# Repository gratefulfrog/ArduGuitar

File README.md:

The ArduGuitar 
==========

Following Microsoft's purchase of Github, this project has migrated to gitlab.

*Electric guitars with Pyboards or Arduinos inside* 

by gratefulfrog on www.arduguitar.org

V2 is now nearly ready with a new, super evolved circuit allowing nearly limitless possiblities (2015 06).  

Although, that seemed true at the time (June 2015), it took another year to get to the first workable version of both the hardware and the software!  As of 4 September 2016, we have bench tested v0.99 of the PyGuitar software and will soon put that sw on the hardware and give it a go! 

The new circuit is  driven by a [Micropython Pyboard](http://micropython.org/).

The whole story is documented [here](https://docs.google.com/document/d/1oo2Q_3ezPv_WPeJZZisc5ifhc270i9kwir6oPctKts0/edit?usp=sharing)!

-------------

V1.1 : ArduStomp and ArduGuitar updated functionality

The ArduStomp pedal interface works well and the updated Android GUI does too!

Now ready to move on to Ardu2 !
-------------

V1.0 : a fully functional Android App with Automation capability!

The sound is near perfect, there are no known bugs! 

Now using a heavily shielded Sparkfun BlueSMIRF bluetooth board and micro_protocol_03 at 115200 baud.

-------------

V0.0 : A working Android App controlling an electric guitar!

The Processing code in the android directory works with the Arduino Micro code in the micro_protocol_02 directory to collectively form the first major milestone of the project: A fully functional android app communicating with the Ibanez RG140 circuit. 

The circuit is controled by an arduino "Micro" and communicates via a JY-MCU bluetooth module.  
        
The Processing code is based on the linux python version in the linux directory. The Ketai Processing library is used for android and bluetooth support.
        
There are too many people to thank individually for all the help and support that they gave me during this work, but the core team of Blake, Enrico, Jean and Luis really made this project possible. The Brussels Hackerspace community also provided great ideas to advance the work.

My profound thanks to them and to all the others!

Now using SSH 2016 12 24

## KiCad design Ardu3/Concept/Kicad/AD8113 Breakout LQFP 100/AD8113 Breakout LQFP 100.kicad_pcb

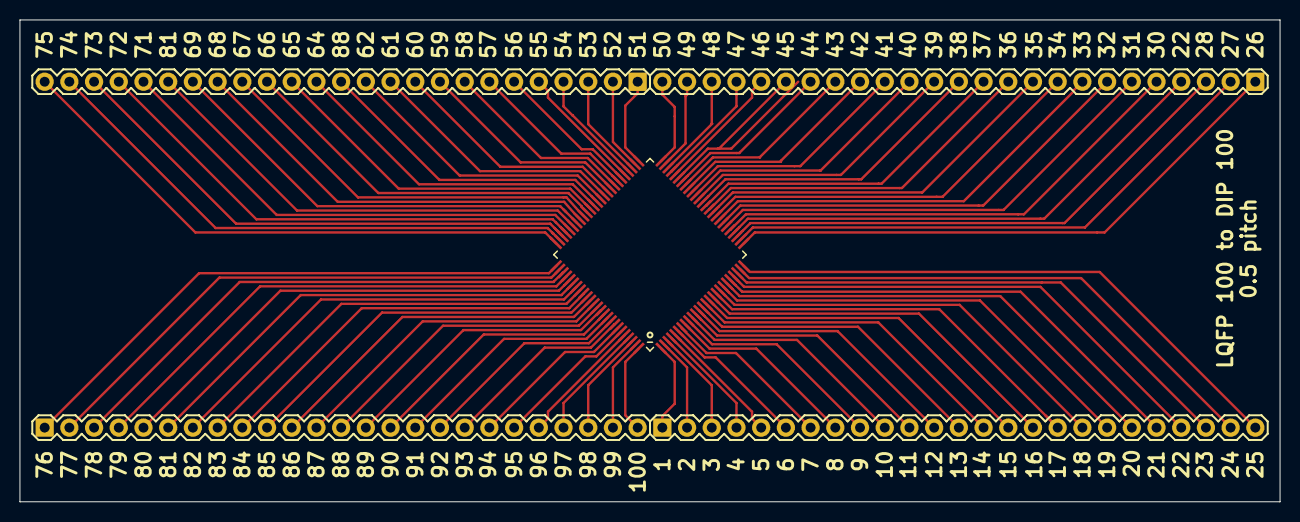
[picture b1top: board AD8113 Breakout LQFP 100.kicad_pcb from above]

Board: 2 copper layers, 129.5 x 49.5 mm, 5 parts (0 on the bottom side), 100 nets.

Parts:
J1, J2, J3, J4: Conn_01x25_Male; 1X25
U1: AD8113JST; AD8113JSTZ

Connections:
/P001: J1.1, U1.1
/P002: J1.2, U1.2
/P003: J1.3, U1.3
/P004: J1.4, U1.4
/P005: J1.5, U1.5
/P006: J1.6, U1.6
/P007: J1.7, U1.7
/P008: J1.8, U1.8
/P009: J1.9, U1.9
/P010: J1.10, U1.10
/P011: J1.11, U1.11
/P012: J1.12, U1.12
/P013: J1.13, U1.13
/P014: J1.14, U1.14
/P015: J1.15, U1.15
/P016: J1.16, U1.16
/P017: J1.17, U1.17
/P018: J1.18, U1.18
/P019: J1.19, U1.19
/P020: J1.20, U1.20
/P021: J1.21, U1.21
/P022: J1.22, U1.22
/P023: J1.23, U1.23
/P024: J1.24, U1.24
/P025: J1.25, U1.25
/P026: J2.1, U1.26
/P027: J2.2, U1.27
/P028: J2.3, U1.28
/P029: J2.4, U1.29
/P030: J2.5, U1.30
/P031: J2.6, U1.31
/P032: J2.7, U1.32
/P033: J2.8, U1.33
/P034: J2.9, U1.34
/P035: J2.10, U1.35
/P036: J2.11, U1.36
/P037: J2.12, U1.37
/P038: J2.13, U1.38
/P039: J2.14, U1.39
/P040: J2.15, U1.40
/P041: J2.16, U1.41
/P042: J2.17, U1.42
/P043: J2.18, U1.43
/P044: J2.19, U1.44
/P045: J2.20, U1.45
/P046: J2.21, U1.46
/P047: J2.22, U1.47
/P048: J2.23, U1.48
/P049: J2.24, U1.49
/P050: J2.25, U1.50
/P051: J3.1, U1.51
/P052: J3.2, U1.52
/P053: J3.3, U1.53
/P054: J3.4, U1.54
/P055: J3.5, U1.55
/P056: J3.6, U1.56
/P057: J3.7, U1.57
/P058: J3.8, U1.58
/P059: J3.9, U1.59
/P060: J3.10, U1.60
/P061: J3.11, U1.61
/P062: J3.12, U1.62
/P063: J3.13, U1.63
/P064: J3.14, U1.64
/P065: J3.15, U1.65
/P066: J3.16, U1.66
/P067: J3.17, U1.67
/P068: J3.18, U1.68
/P069: J3.19, U1.69
/P070: J3.20, U1.70
/P071: J3.21, U1.71
/P072: J3.22, U1.72
/P073: J3.23, U1.73
/P074: J3.24, U1.74
/P075: J3.25, U1.75
/P076: J4.1, U1.76
/P077: J4.2, U1.77
/P078: J4.3, U1.78
/P079: J4.4, U1.79
/P080: J4.5, U1.80
/P081: J4.6, U1.81
/P082: J4.7, U1.82
/P083: J4.8, U1.83
/P084: J4.9, U1.84
/P085: J4.10, U1.85
/P086: J4.11, U1.86
/P087: J4.12, U1.87
/P088: J4.13, U1.88
/P089: J4.14, U1.89
/P090: J4.15, U1.90
/P091: J4.16, U1.91
/P092: J4.17, U1.92
/P093: J4.18, U1.93
/P094: J4.19, U1.94
/P095: J4.20, U1.95
/P096: J4.21, U1.96
/P097: J4.22, U1.97
/P098: J4.23, U1.98
/P099: J4.24, U1.99
/P100: J4.25, U1.100

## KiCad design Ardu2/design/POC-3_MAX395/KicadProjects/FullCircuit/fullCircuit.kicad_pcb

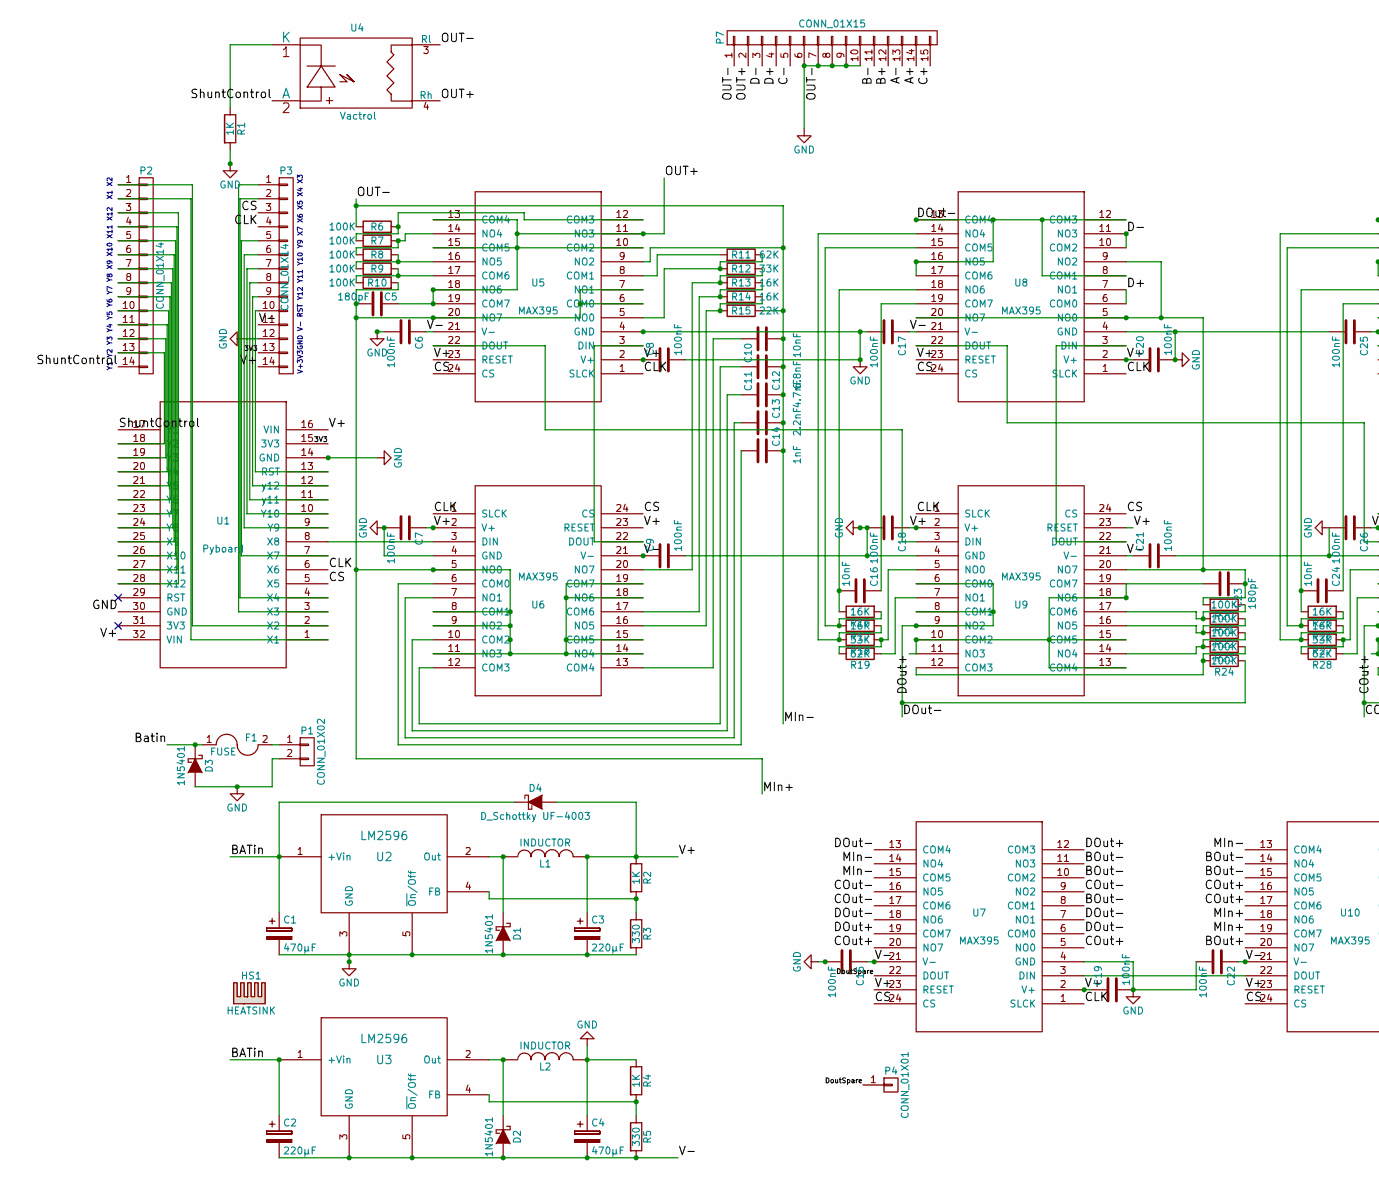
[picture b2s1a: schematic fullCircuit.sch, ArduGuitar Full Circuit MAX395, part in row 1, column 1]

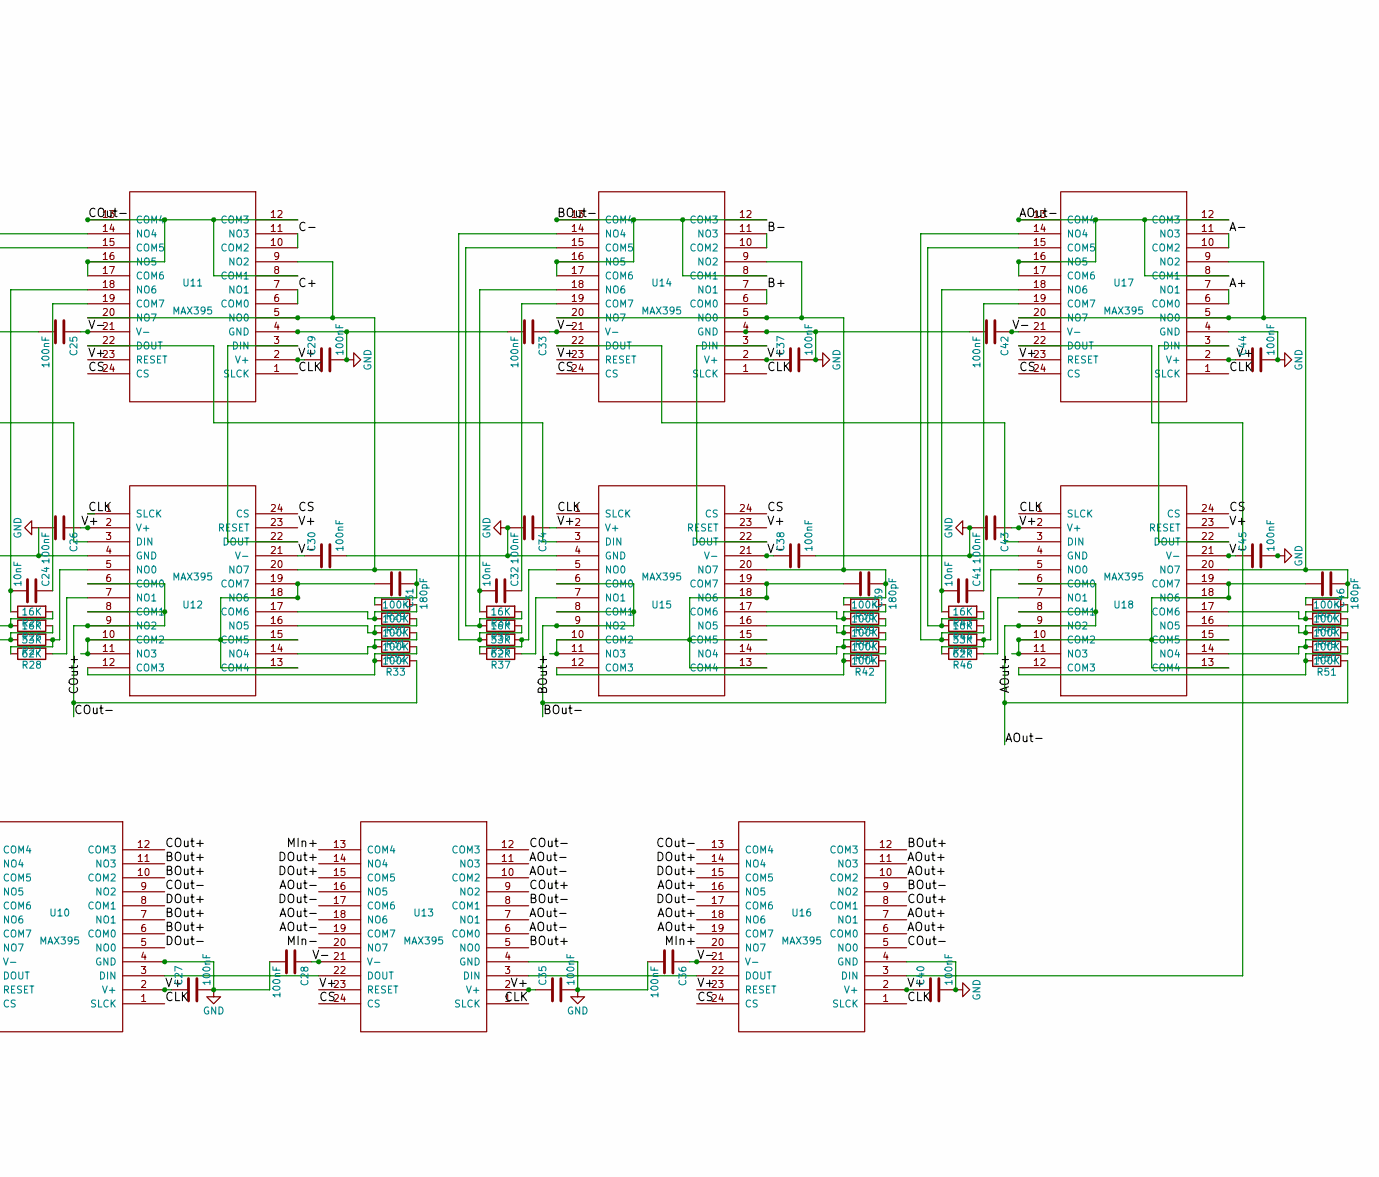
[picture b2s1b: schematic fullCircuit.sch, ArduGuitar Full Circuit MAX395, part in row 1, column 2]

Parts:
C1, C4: 470µF; C_Radial_D10_L16_P5
C2, C3: 220µF; C_Radial_D8_L11.5_P3.5
C5, C23, C31, C39, C46: 180pF; C_Disc_D3_P2.5
C6, C7, C8, C9, C15, C17, C18, C19, C20, C21, C22, C25, C26, C27, C28, C29, C30, C33, C34, C35, C36, C37, C38, C40, C42, C43, C44, C45: 100nF; C_Disc_D3_P2.5
C10, C16, C24, C32, C41: 10nF; C_Disc_D6_P5
C11: 6.8nF; C_Disc_D6_P5
C12: 4.7nF; C_Disc_D6_P5
C13: 2.2nF; C_Disc_D6_P5
C14: 1nF; C_Disc_D6_P5
D1, D2, D3: 1N5401; Diode_DO-201AD_Horizontal_RM15
D4: D_Schottky UF-4003; Diode_DO-41_SOD81_Horizontal_RM10
F1: FUSE; Fuse_TE5_Littlefuse-395Series
HS1: HEATSINK; Heatsink_TO_220_38_20
L1, L2: INDUCTOR; 330L-Q9N_Inductor
P1: CONN_01X02; PINHEAD1-2
P2, P3: CONN_01X14; Pin_Header_Straight_1x14
P4: CONN_01X01; Pin_Header_Straight_1x01
P7: CONN_01X15; DB_15F-VGA_00_BOB
R1, R2, R4: 1K; Resistor_Horizontal_RM10mm
R3, R5: 330; Resistor_Horizontal_RM10mm
R6, R7, R8, R9, R10, R20, R21, R22, R23, R24, R29, R30, R31, R32, R33, R38, R39, R40, R41, R42, R47, R48, R49, R50, R51: 100K; Resistor_Horizontal_RM10mm
R11, R19, R28, R37, R46: 62K; Resistor_Horizontal_RM10mm
R12, R18, R27, R36, R45: 33K; Resistor_Horizontal_RM10mm
R13, R14, R16, R17, R25, R26, R34, R35, R43, R44: 16K; Resistor_Horizontal_RM10mm
R15: 22K; Resistor_Horizontal_RM10mm
U1: Pyboard; Pyboard16x2
U2, U3: LM2596; T05D
U4: Vactrol
U5, U6, U7, U8, U9, U10, U11, U12, U13, U14, U15, U16, U17, U18: MAX395; DIP-24__300_pads_70_10

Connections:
/3V3: P3.13, U1.15 (3V3)
/A+: P7.14, U17.6 (COM0), U17.7 (NO1)
/A-: P7.13, U17.10 (COM2), U17.11 (NO3)
/AOut+: C46.2, U16.6 (COM0), U16.7 (NO1), U16.10 (COM2), U16.11 (NO3), U16.16 (NO5), U16.18 (NO6), U16.19 (COM7), U18.10 (COM2), U18.11 (NO3), U18.13 (COM4), U18.15 (COM5), U18.18 (NO6), U18.19 (COM7)
/AOut-: R51.1, U13.6 (COM0), U13.7 (NO1), U13.10 (COM2), U13.11 (NO3), U13.16 (NO5), U13.18 (NO6), U13.19 (COM7), U17.8 (COM1), U17.12 (COM3), U17.13 (COM4), U17.16 (NO5), U17.17 (COM6), U18.6 (COM0), U18.8 (COM1), U18.9 (NO2)
/B+: P7.12, U14.6 (COM0), U14.7 (NO1)
/B-: P7.11, U14.10 (COM2), U14.11 (NO3)
/BATin: C1.1, C2.1, D3.1 (K), D4.1 (K), F1.1, U2.1 (+Vin), U3.1 (+Vin)
/BOut+: C39.2, U10.6 (COM0), U10.7 (NO1), U10.10 (COM2), U10.11 (NO3), U10.20 (NO7), U13.5 (NO0), U15.10 (COM2), U15.11 (NO3), U15.13 (COM4), U15.15 (COM5), U15.18 (NO6), U15.19 (COM7), U16.12 (COM3)
/BOut-: R42.1, U7.8 (COM1), U7.10 (COM2), U7.11 (NO3), U10.14 (NO4), U10.15 (COM5), U13.8 (COM1), U14.8 (COM1), U14.12 (COM3), U14.13 (COM4), U14.16 (NO5), U14.17 (COM6), U15.6 (COM0), U15.8 (COM1), U15.9 (NO2), U16.9 (NO2)
/C+: P7.15, U11.6 (COM0), U11.7 (NO1)
/C-: P7.5, U11.10 (COM2), U11.11 (NO3)
/CLK: P3.4, U1.6 (X6), U5.1 (SLCK), U6.1 (SLCK), U7.1 (SLCK), U8.1 (SLCK), U9.1 (SLCK), U10.1 (SLCK), U11.1 (SLCK), U12.1 (SLCK), U13.1 (SLCK), U14.1 (SLCK), U15.1 (SLCK), U16.1 (SLCK), U17.1 (SLCK), U18.1 (SLCK)
/COut+: C31.2, U7.5 (NO0), U7.20 (NO7), U10.12 (COM3), U10.16 (NO5), U10.17 (COM6), U12.10 (COM2), U12.11 (NO3), U12.13 (COM4), U12.15 (COM5), U12.18 (NO6), U12.19 (COM7), U13.9 (NO2), U16.8 (COM1)
/COut-: R33.1, U7.9 (NO2), U7.16 (NO5), U7.17 (COM6), U10.9 (NO2), U11.8 (COM1), U11.12 (COM3), U11.13 (COM4), U11.16 (NO5), U11.17 (COM6), U12.6 (COM0), U12.8 (COM1), U12.9 (NO2), U13.12 (COM3), U16.5 (NO0), U16.13 (COM4)
/CS: P3.3, U1.5 (X5), U5.24 (CS), U6.24 (CS), U7.24 (CS), U8.24 (CS), U9.24 (CS), U10.24 (CS), U11.24 (CS), U12.24 (CS), U13.24 (CS), U14.24 (CS), U15.24 (CS), U16.24 (CS), U17.24 (CS), U18.24 (CS)
/D+: P7.4, U8.6 (COM0), U8.7 (NO1)
/D-: P7.3, U8.10 (COM2), U8.11 (NO3)
/DOut+: C23.2, U7.12 (COM3), U7.19 (COM7), U9.10 (COM2), U9.11 (NO3), U9.13 (COM4), U9.15 (COM5), U9.18 (NO6), U9.19 (COM7), U10.8 (COM1), U13.14 (NO4), U13.15 (COM5), U16.14 (NO4), U16.15 (COM5)
/DOut-: R24.1, U7.6 (COM0), U7.7 (NO1), U7.13 (COM4), U7.18 (NO6), U8.8 (COM1), U8.12 (COM3), U8.13 (COM4), U8.16 (NO5), U8.17 (COM6), U9.6 (COM0), U9.8 (COM1), U9.9 (NO2), U10.5 (NO0), U13.17 (COM6), U16.17 (COM6)
/DoutSpare: P4.1, U7.22 (DOUT)
/MIn+: C5.1, R10.2, U5.6 (COM0), U5.7 (NO1), U5.20 (NO7), U6.5 (NO0), U6.8 (COM1), U6.9 (NO2), U6.11 (NO3), U6.14 (NO4), U6.15 (COM5), U6.18 (NO6), U6.19 (COM7), U10.18 (NO6), U10.19 (COM7), U13.13 (COM4), U16.20 (NO7)
/OUT+: C5.2, P7.2, U4.4 (Rh), U5.10 (COM2), U5.11 (NO3), U5.13 (COM4), U5.15 (COM5), U5.18 (NO6), U5.19 (COM7)
/ShuntControl: P2.14, U1.17 (Y1), U4.2 (A)
/V+: C3.1, C7.1, C8.1, C18.1, C19.1, C20.1, C26.1, C27.1, C29.1, C34.1, C35.1, C37.1, C40.1, C43.1, C44.1, D4.2 (A), L1.2, P3.14, R2.1, U1.16 (VIN), U1.32 (VIN), U5.2 (V+), U5.23 (RESET), U6.2 (V+), U6.23 (RESET), U7.2 (V+), U7.23 (RESET), U8.2 (V+), U8.23 (RESET), U9.2 (V+), U9.23 (RESET), U10.2 (V+), U10.23 (RESET), U11.2 (V+), U11.23 (RESET), U12.2 (V+), U12.23 (RESET), U13.2 (V+), U13.23 (RESET), U14.2 (V+), U14.23 (RESET), U15.2 (V+), U15.23 (RESET), U16.2 (V+), U16.23 (RESET), U17.2 (V+), U17.23 (RESET), U18.2 (V+), U18.23 (RESET)
/V-: C2.2, C4.2, C6.1, C9.1, C15.1, C17.1, C21.1, C22.1, C25.1, C28.1, C30.1, C33.1, C36.1, C38.1, C42.1, C45.1, D2.2 (A), P3.11, R5.2, U3.3 (GND), U3.5 (~On~/Off), U5.21 (V-), U6.21 (V-), U7.21 (V-), U8.21 (V-), U9.21 (V-), U10.21 (V-), U11.21 (V-), U12.21 (V-), U13.21 (V-), U14.21 (V-), U15.21 (V-), U16.21 (V-), U17.21 (V-), U18.21 (V-)
unnamed: C10.1, U6.13 (COM4)
unnamed: C11.1, U6.12 (COM3)
unnamed: C12.2, U6.10 (COM2)
unnamed: C13.2, U6.7 (NO1)
unnamed: C14.2, U6.6 (COM0)
unnamed: C16.1, U8.19 (COM7)
unnamed: C16.2, R16.1, U8.18 (NO6)
unnamed: C23.1, R20.2, U8.5 (NO0), U8.9 (NO2), U8.20 (NO7), U9.20 (NO7)
unnamed: C24.1, U11.19 (COM7)
unnamed: C24.2, R25.1, U11.18 (NO6)
unnamed: C31.1, R29.2, U11.5 (NO0), U11.9 (NO2), U11.20 (NO7), U12.20 (NO7)
unnamed: C32.1, U14.19 (COM7)
unnamed: C32.2, R34.1, U14.18 (NO6)
unnamed: C39.1, R38.2, U14.5 (NO0), U14.9 (NO2), U14.20 (NO7), U15.20 (NO7)
unnamed: C41.1, U17.19 (COM7)
unnamed: C41.2, R43.1, U17.18 (NO6)
unnamed: C46.1, R47.2, U17.5 (NO0), U17.9 (NO2), U17.20 (NO7), U18.20 (NO7)
unnamed: D1.1 (K), L1.1, U2.2 (Out)
unnamed: D2.1 (K), L2.1, U3.2 (Out)
unnamed: F1.2, P1.1
unnamed: P2.1, U1.2 (X2)
unnamed: P2.2, U1.1 (X1)
unnamed: P2.3, U1.28 (X12)
unnamed: P2.4, U1.27 (X11)
unnamed: P2.5, U1.26 (X10)
unnamed: P2.6, U1.25 (X9)
unnamed: P2.7, U1.24 (Y8)
unnamed: P2.8, U1.23 (Y7)
unnamed: P2.9, U1.22 (Y6)
unnamed: P2.10, U1.21 (Y5)
unnamed: P2.11, U1.20 (Y4)
unnamed: P2.12, U1.19 (Y3)
unnamed: P2.13, U1.18 (Y2)
unnamed: P3.1, U1.3 (X3)
unnamed: P3.2, U1.4 (X4)
unnamed: P3.5, U1.7 (X7)
unnamed: P3.7, U1.10 (Y10)
unnamed: P3.8, U1.11 (y11)
unnamed: P3.9, U1.12 (y12)
unnamed: P3.10, U1.13 (RST)
unnamed: R1.1, U4.1 (K)
unnamed: R2.2, R3.1, U2.4 (FB)
unnamed: R4.2, R5.1, U3.4 (FB)
unnamed: R6.2, R7.1, U5.12 (COM3)
unnamed: R7.2, R8.1, U5.14 (NO4)
unnamed: R8.2, R9.1, U5.16 (NO5)
unnamed: R9.2, R10.1, U5.17 (COM6)
unnamed: R11.1, R12.2, U5.5 (NO0)
unnamed: R11.2, U5.8 (COM1)
unnamed: R12.1, R13.2, U6.20 (NO7)
unnamed: R13.1, R14.2, U6.17 (COM6)
unnamed: R14.1, R15.2, U6.16 (NO5)
unnamed: R16.2, R17.1, U8.15 (COM5)
unnamed: R17.2, R18.1, U8.14 (NO4)
unnamed: R18.2, R19.1, U9.5 (NO0)
unnamed: R19.2, U9.7 (NO1)
unnamed: R20.1, R21.2, U9.17 (COM6)
unnamed: R21.1, R22.2, U9.16 (NO5)
unnamed: R22.1, R23.2, U9.14 (NO4)
unnamed: R23.1, R24.2, U9.12 (COM3)
unnamed: R25.2, R26.1, U11.15 (COM5)
unnamed: R26.2, R27.1, U11.14 (NO4)
unnamed: R27.2, R28.1, U12.5 (NO0)
unnamed: R28.2, U12.7 (NO1)
unnamed: R29.1, R30.2, U12.17 (COM6)
unnamed: R30.1, R31.2, U12.16 (NO5)
unnamed: R31.1, R32.2, U12.14 (NO4)
unnamed: R32.1, R33.2, U12.12 (COM3)
unnamed: R34.2, R35.1, U14.15 (COM5)
unnamed: R35.2, R36.1, U14.14 (NO4)
unnamed: R36.2, R37.1, U15.5 (NO0)
unnamed: R37.2, U15.7 (NO1)
unnamed: R38.1, R39.2, U15.17 (COM6)
unnamed: R39.1, R40.2, U15.16 (NO5)
unnamed: R40.1, R41.2, U15.14 (NO4)
unnamed: R41.1, R42.2, U15.12 (COM3)
unnamed: R43.2, R44.1, U17.15 (COM5)
unnamed: R44.2, R45.1, U17.14 (NO4)
unnamed: R45.2, R46.1, U18.5 (NO0)
unnamed: R46.2, U18.7 (NO1)
unnamed: R47.1, R48.2, U18.17 (COM6)
unnamed: R48.1, R49.2, U18.16 (NO5)
unnamed: R49.1, R50.2, U18.14 (NO4)
unnamed: R50.1, R51.2, U18.12 (COM3)
unnamed: U1.8 (X8), U6.3 (DIN)
unnamed: U5.3 (DIN), U6.22 (DOUT)
unnamed: U5.22 (DOUT), U9.3 (DIN)
unnamed: U8.3 (DIN), U9.22 (DOUT)
unnamed: U10.3 (DIN), U13.22 (DOUT)
unnamed: U7.3 (DIN), U10.22 (DOUT)
unnamed: U11.3 (DIN), U12.22 (DOUT)
unnamed: U11.22 (DOUT), U15.3 (DIN)
unnamed: U8.22 (DOUT), U12.3 (DIN)
unnamed: U13.3 (DIN), U16.22 (DOUT)
unnamed: U14.3 (DIN), U15.22 (DOUT)
unnamed: U14.22 (DOUT), U18.3 (DIN)
unnamed: U16.3 (DIN), U17.22 (DOUT)
unnamed: U17.3 (DIN), U18.22 (DOUT)

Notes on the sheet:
Y1 Y2 Y3 Y4 Y5 Y6 Y7 Y8 X9 X10 X11 X12 X1 X2
V+3V3GND V- RST Y12 Y11 Y10 Y9 X7 X6 X5 X4 X3

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
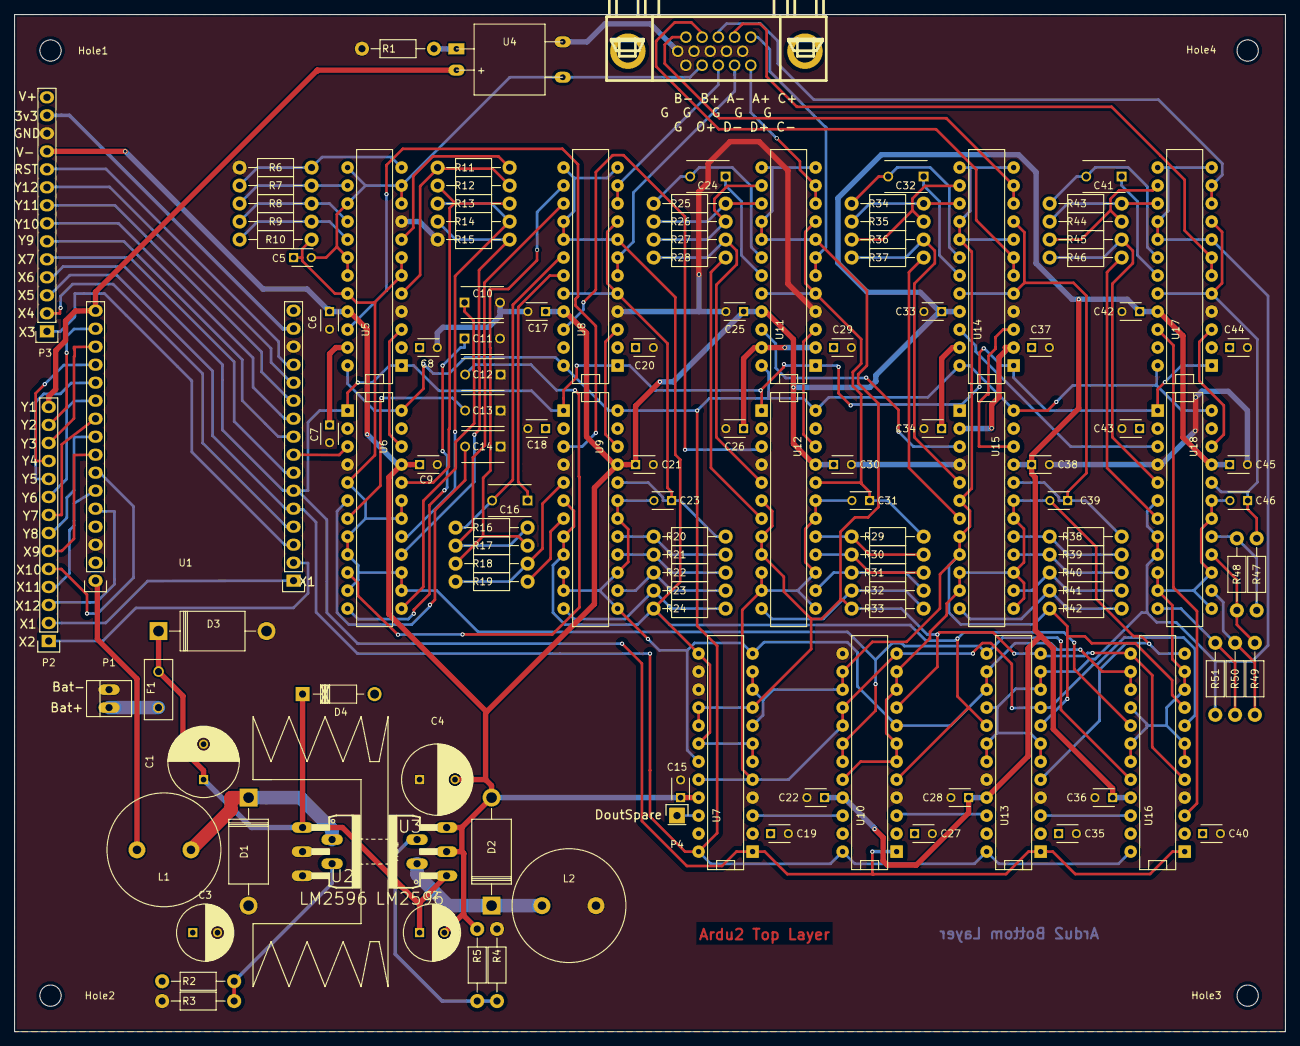
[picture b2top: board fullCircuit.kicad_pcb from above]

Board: 2 copper layers, 179.3 x 143.5 mm, 132 parts (0 on the bottom side), 126 nets.

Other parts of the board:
Hole1, Hole2, Hole3, Hole4: MountingHole_3mm

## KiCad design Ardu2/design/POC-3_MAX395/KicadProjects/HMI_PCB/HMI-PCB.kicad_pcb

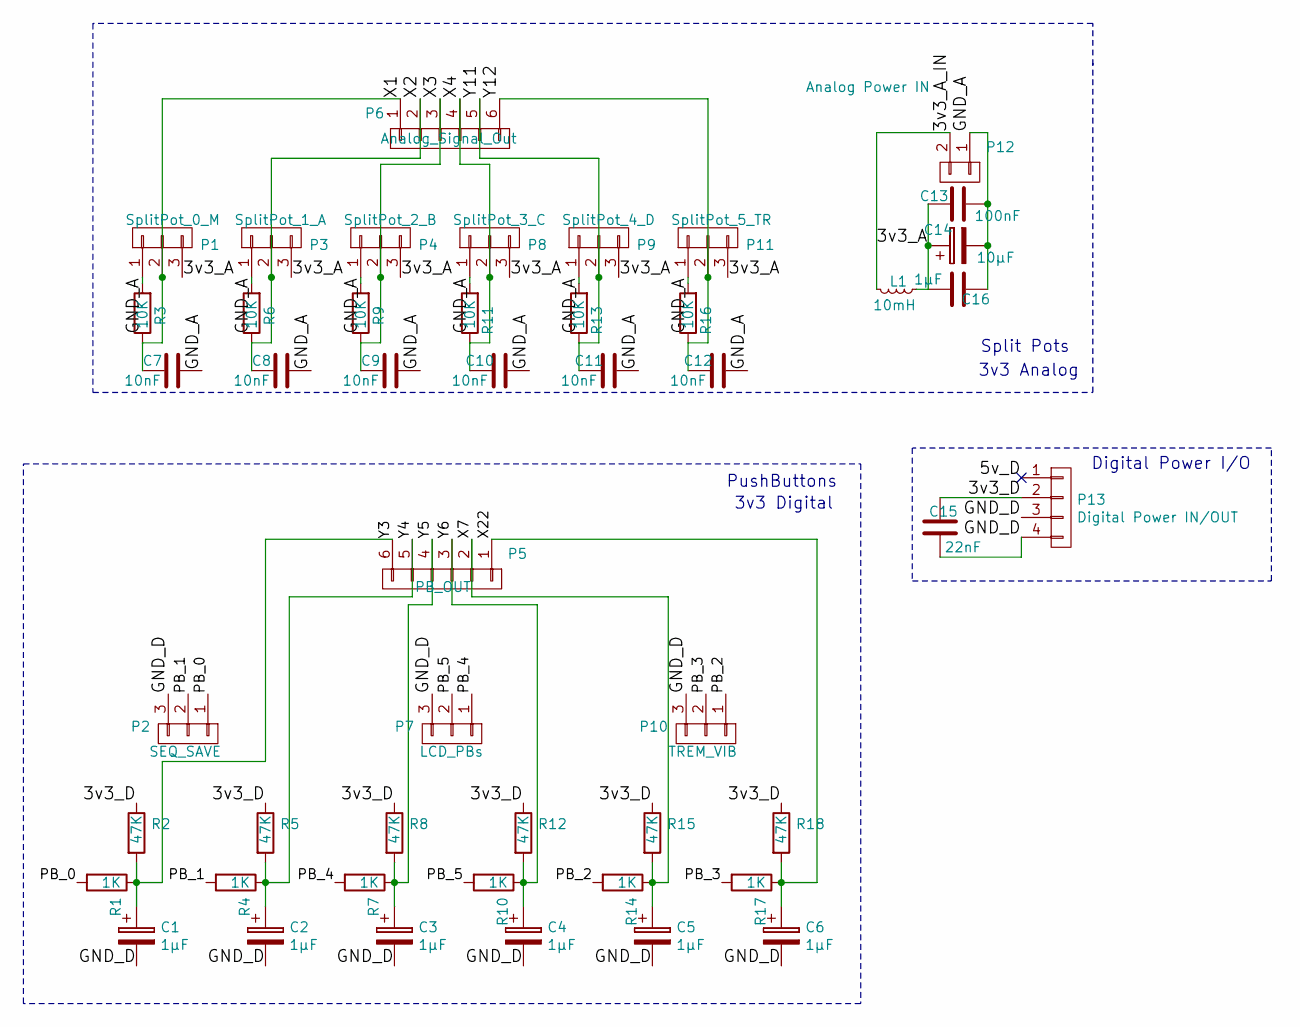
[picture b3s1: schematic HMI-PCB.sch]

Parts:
C1, C2, C3, C4, C5, C6: 1µF; C_Radial_D5_L11_P3.81
C7, C8, C9, C10, C11, C12: 10nF; C_Disc_D6_P5
C13: 100nF; C_Disc_D3_P2.5
C14: 10µF; C_Disc_D3_P2.5
C15: 22nF; C_Rect_L7_W2.5_P5
C16: 1µF; C_Disc_D3_P2.5
L1: 10mH; Choke_Radial_D13_P10_10mH
P1: SplitPot_0_M; Wafer_Angled_1x03_1mm_hole
P2: SEQ_SAVE; Wafer_Angled_1x03_1mm_hole
P3: SplitPot_1_A; Wafer_Angled_1x03_1mm_hole
P4: SplitPot_2_B; Wafer_Angled_1x03_1mm_hole
P5: PB_OUT; Wafer_Angled_1x06_1mm_Hole
P6: Analog_Signal_Out; Wafer_Angled_1x06_1mm_Hole
P7: LCD_PBs; Wafer_Angled_1x03_1mm_hole
P8: SplitPot_3_C; Wafer_Angled_1x03_1mm_hole
P9: SplitPot_4_D; Wafer_Angled_1x03_1mm_hole
P10: TREM_VIB; Wafer_Angled_1x03_1mm_hole
P11: SplitPot_5_TR; Wafer_Angled_1x03_1mm_hole
P12: Analog Power IN; Wafer_Angled_1x02_1mm_hole
P13: Digital Power IN/OUT; bornier4_Dinkle
R1, R4, R7, R10, R14, R17: 1K; Resistor_Horizontal_RM7mm_Big_Pads
R2, R5, R8, R12, R15, R18: 47K; Resistor_Horizontal_RM20mm_Big_Pads
R3, R6, R9, R11, R13, R16: 10K; Resistor_Horizontal_RM7mm_Big_Pads

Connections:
/3v3_A: C13.2, C14.1, C16.1, L1.1, P1.3, P3.3, P4.3, P8.3, P9.3, P11.3
/3v3_A_IN: L1.2, P12.2
/3v3_D: C15.1, P13.2, R2.1, R5.1, R8.1, R12.1, R15.1, R18.1
/GND_A: C7.1, C8.1, C9.1, C10.1, C11.1, C12.1, C13.1, C14.2, C16.2, P1.1, P3.1, P4.1, P8.1, P9.1, P11.1, P12.1, R3.2, R6.2, R9.2, R11.2, R13.2, R16.2
/GND_D: C1.2, C2.2, C3.2, C4.2, C5.2, C6.2, C15.2, P2.3, P7.3, P10.3, P13.3, P13.4
/PB_0: P2.1, R1.2
/PB_1: P2.2, R4.2
/PB_2: P10.1, R14.2
/PB_3: P10.2, R17.2
/PB_4: P7.1, R7.2
/PB_5: P7.2, R10.2
/X1: C7.2, P1.2, P6.1, R3.1
/X2: C8.2, P3.2, P6.2, R6.1
/X3: C9.2, P4.2, P6.3, R9.1
/X4: C10.2, P6.4, P8.2, R11.1
/X7: C5.1, P5.2, R14.1, R15.2
/X22: C6.1, P5.1, R17.1, R18.2
/Y3: C1.1, P5.6, R1.1, R2.2
/Y4: C2.1, P5.5, R4.1, R5.2
/Y5: C3.1, P5.4, R7.1, R8.2
/Y6: C4.1, P5.3, R10.1, R12.2
/Y11: C11.2, P6.5, P9.2, R13.1
/Y12: C12.2, P6.6, P11.2, R16.1

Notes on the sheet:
Split Pots
PushButtons
3v3 Digital
3v3 Analog
Digital Power I/O

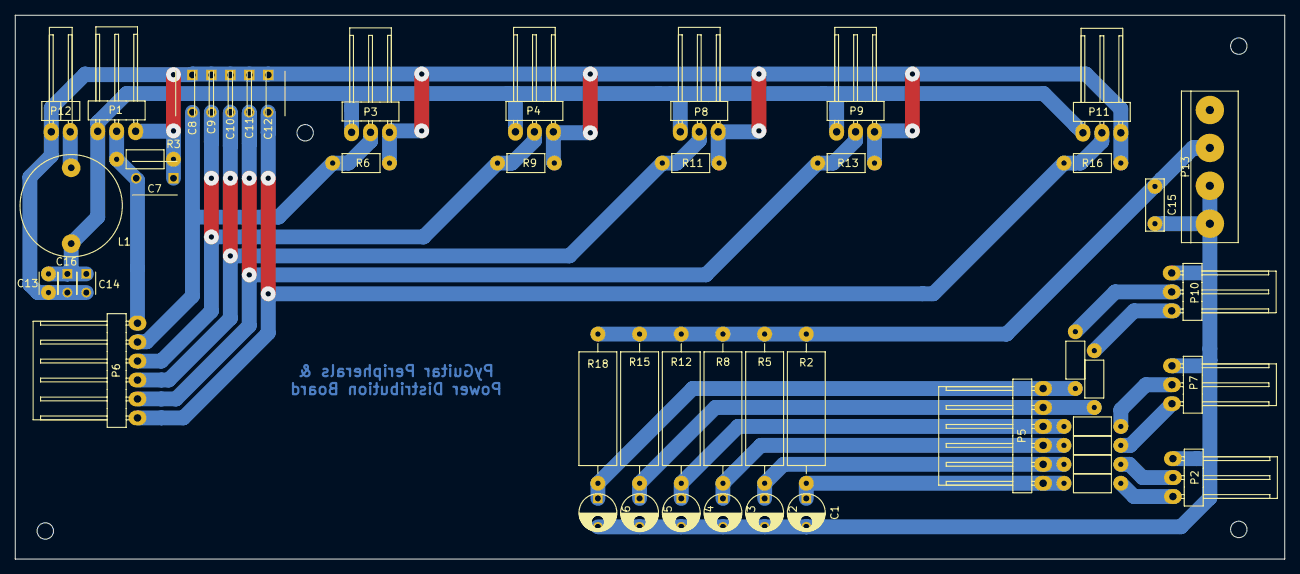
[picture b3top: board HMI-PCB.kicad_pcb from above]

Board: 2 copper layers, 170.2 x 72.9 mm, 48 parts (0 on the bottom side), 23 nets.

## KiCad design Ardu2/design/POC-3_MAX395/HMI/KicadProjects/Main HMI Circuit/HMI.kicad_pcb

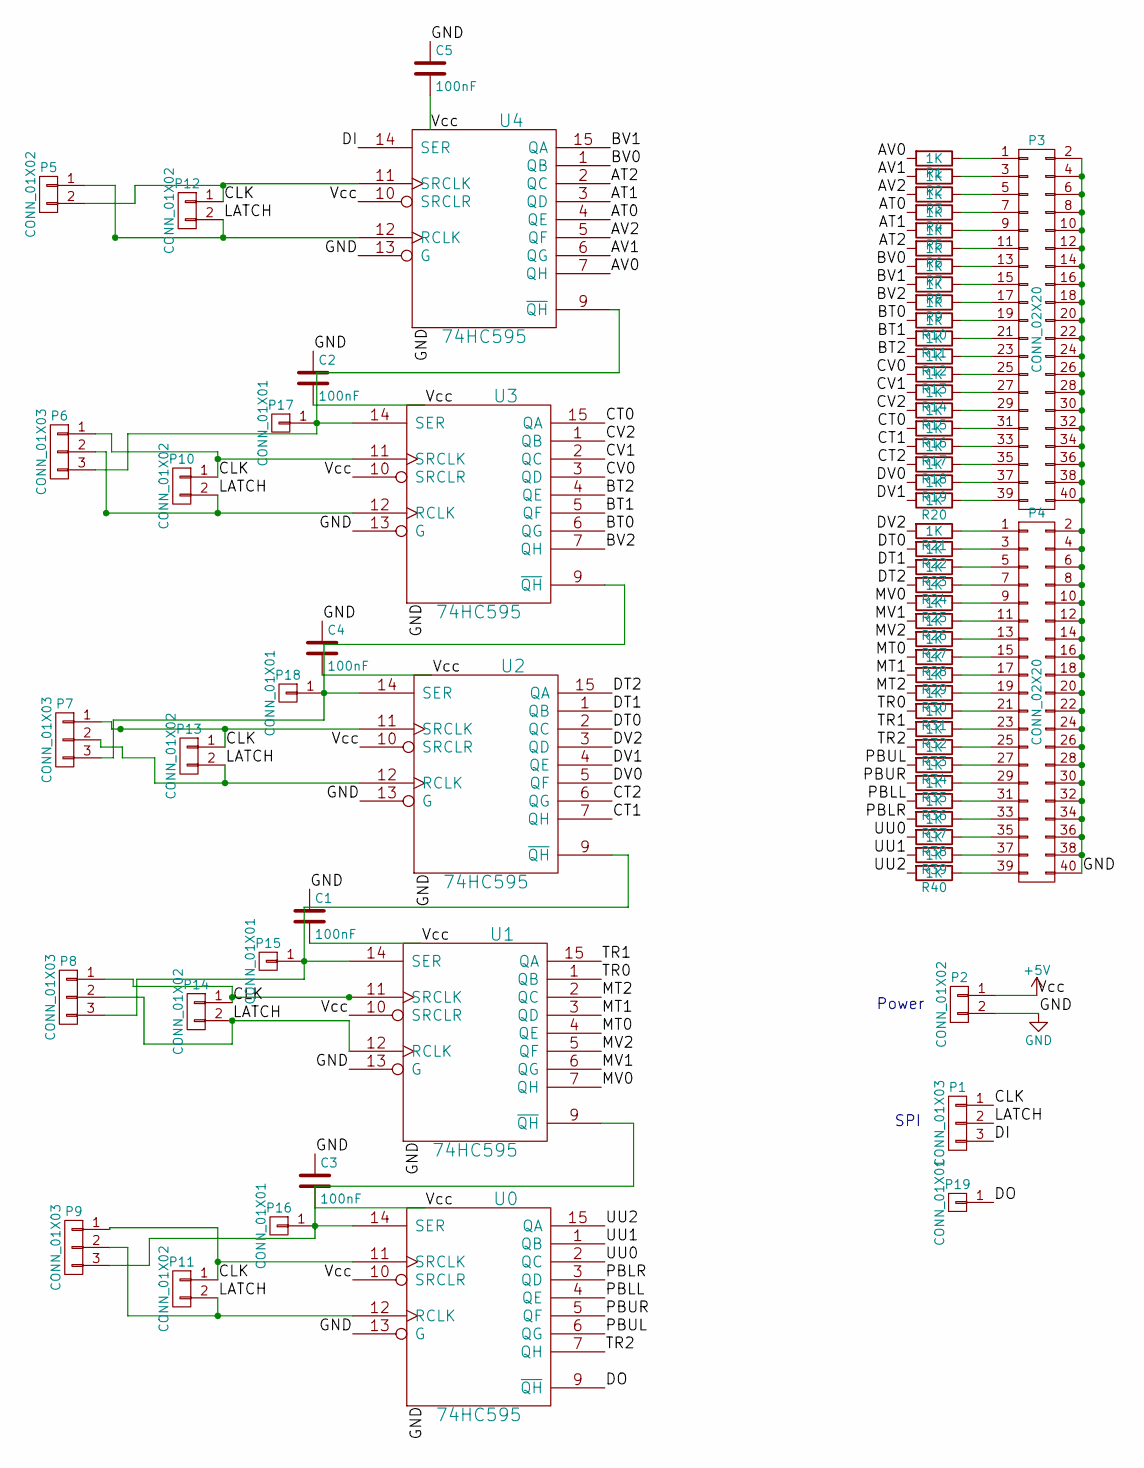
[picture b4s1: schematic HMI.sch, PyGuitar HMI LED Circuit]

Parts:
C1, C2, C3, C4, C5: 100nF; C_Disc_D3_P2.5
P1, P6, P7, P8, P9: CONN_01X03; Pin_Header_Straight_1x03
P2, P5, P10, P11, P12, P13, P14: CONN_01X02; Pin_Header_Straight_1x02
P3, P4: CONN_02X20; Pin_Header_Straight_2x20
P15, P16, P17, P18, P19: CONN_01X01; Pin_Header_Straight_1x01
R1, R2, R3, R4, R5, R6, R7, R8, R9, R10, R11, R12, R13, R14, R15, R16, R17, R18, R19, R20, R21, R22, R23, R24, R25, R26, R27, R28, R29, R30, R31, R32, R33, R34, R35, R36, R37, R38, R39, R40: 1K; Resistor_Horizontal_RM10mm
U0, U1, U2, U3, U4: 74HC595; DIP-16_W7.62mm

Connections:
+5V: C1.2, C2.2, C3.2, C4.2, C5.2, P2.1, U0.10 (SRCLR), U0.16 (VCC), U1.10 (SRCLR), U1.16 (VCC), U2.10 (SRCLR), U2.16 (VCC), U3.10 (SRCLR), U3.16 (VCC), U4.10 (SRCLR), U4.16 (VCC)
/AT0: R4.2, U4.4 (QE)
/AT1: R5.2, U4.3 (QD)
/AT2: R6.2, U4.2 (QC)
/AV0: R1.2, U4.7 (QH)
/AV1: R2.2, U4.6 (QG)
/AV2: R3.2, U4.5 (QF)
/BT0: R10.2, U3.6 (QG)
/BT1: R11.2, U3.5 (QF)
/BT2: R12.2, U3.4 (QE)
/BV0: R7.2, U4.1 (QB)
/BV1: R8.2, U4.15 (QA)
/BV2: R9.2, U3.7 (QH)
/CLK: P1.1, P5.2, P6.1, P7.1, P8.1, P9.1, P10.1, P11.1, P12.1, P13.1, P14.1, U0.11 (SRCLK), U1.11 (SRCLK), U2.11 (SRCLK), U3.11 (SRCLK), U4.11 (SRCLK)
/CT0: R16.2, U3.15 (QA)
/CT1: R17.2, U2.7 (QH)
/CT2: R18.2, U2.6 (QG)
/CV0: R13.2, U3.3 (QD)
/CV1: R14.2, U3.2 (QC)
/CV2: R15.2, U3.1 (QB)
/DI: P1.3, U4.14 (SER)
/DO: P19.1, U0.9 (~QH)
/DT0: R22.2, U2.2 (QC)
/DT1: R23.2, U2.1 (QB)
/DT2: R24.2, U2.15 (QA)
/DV0: R19.2, U2.5 (QF)
/DV1: R20.2, U2.4 (QE)
/DV2: R21.2, U2.3 (QD)
/LATCH: P1.2, P5.1, P6.2, P7.2, P8.2, P9.2, P10.2, P11.2, P12.2, P13.2, P14.2, U0.12 (RCLK), U1.12 (RCLK), U2.12 (RCLK), U3.12 (RCLK), U4.12 (RCLK)
/MT0: R28.2, U1.4 (QE)
/MT1: R29.2, U1.3 (QD)
/MT2: R30.2, U1.2 (QC)
/MV0: R25.2, U1.7 (QH)
/MV1: R26.2, U1.6 (QG)
/MV2: R27.2, U1.5 (QF)
/PBLL: R36.2, U0.4 (QE)
/PBLR: R37.2, U0.3 (QD)
/PBUL: R34.2, U0.6 (QG)
/PBUR: R35.2, U0.5 (QF)
/TR0: R31.2, U1.1 (QB)
/TR1: R32.2, U1.15 (QA)
/TR2: R33.2, U0.7 (QH)
/UU0: R38.2, U0.2 (QC)
/UU1: R39.2, U0.1 (QB)
/UU2: R40.2, U0.15 (QA)
GND: C1.1, C2.1, C3.1, C4.1, C5.1, P2.2, P3.2, P3.4, P3.6, P3.8, P3.10, P3.12, P3.14, P3.16, P3.18, P3.20, P3.22, P3.24, P3.26, P3.28, P3.30, P3.32, P3.34, P3.36, P3.38, P3.40, P4.2, P4.4, P4.6, P4.8, P4.10, P4.12, P4.14, P4.16, P4.18, P4.20, P4.22, P4.24, P4.26, P4.28, P4.30, P4.32, P4.34, P4.36, P4.38, P4.40, U0.8 (GND), U0.13 (G), U1.8 (GND), U1.13 (G), U2.8 (GND), U2.13 (G), U3.8 (GND), U3.13 (G), U4.8 (GND), U4.13 (G)
unnamed: P3.1, R1.1
unnamed: P3.3, R2.1
unnamed: P3.5, R3.1
unnamed: P3.7, R4.1
unnamed: P3.9, R5.1
unnamed: P3.11, R6.1
unnamed: P3.13, R7.1
unnamed: P3.15, R8.1
unnamed: P3.17, R9.1
unnamed: P3.19, R10.1
unnamed: P3.21, R11.1
unnamed: P3.23, R12.1
unnamed: P3.25, R13.1
unnamed: P3.27, R14.1
unnamed: P3.29, R15.1
unnamed: P3.31, R16.1
unnamed: P3.33, R17.1
unnamed: P3.35, R18.1
unnamed: P3.37, R19.1
unnamed: P3.39, R20.1
unnamed: P4.1, R21.1
unnamed: P4.3, R22.1
unnamed: P4.5, R23.1
unnamed: P4.7, R24.1
unnamed: P4.9, R25.1
unnamed: P4.11, R26.1
unnamed: P4.13, R27.1
unnamed: P4.15, R28.1
unnamed: P4.17, R29.1
unnamed: P4.19, R30.1
unnamed: P4.21, R31.1
unnamed: P4.23, R32.1
unnamed: P4.25, R33.1
unnamed: P4.27, R34.1
unnamed: P4.29, R35.1
unnamed: P4.31, R36.1
unnamed: P4.33, R37.1
unnamed: P4.35, R38.1
unnamed: P4.37, R39.1
unnamed: P4.39, R40.1
unnamed: P8.3, P15.1, U1.14 (SER), U2.9 (~QH)
unnamed: P9.3, P16.1, U0.14 (SER), U1.9 (~QH)
unnamed: P6.3, P17.1, U3.14 (SER), U4.9 (~QH)
unnamed: P7.3, P18.1, U2.14 (SER), U3.9 (~QH)

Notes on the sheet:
Power
SPI

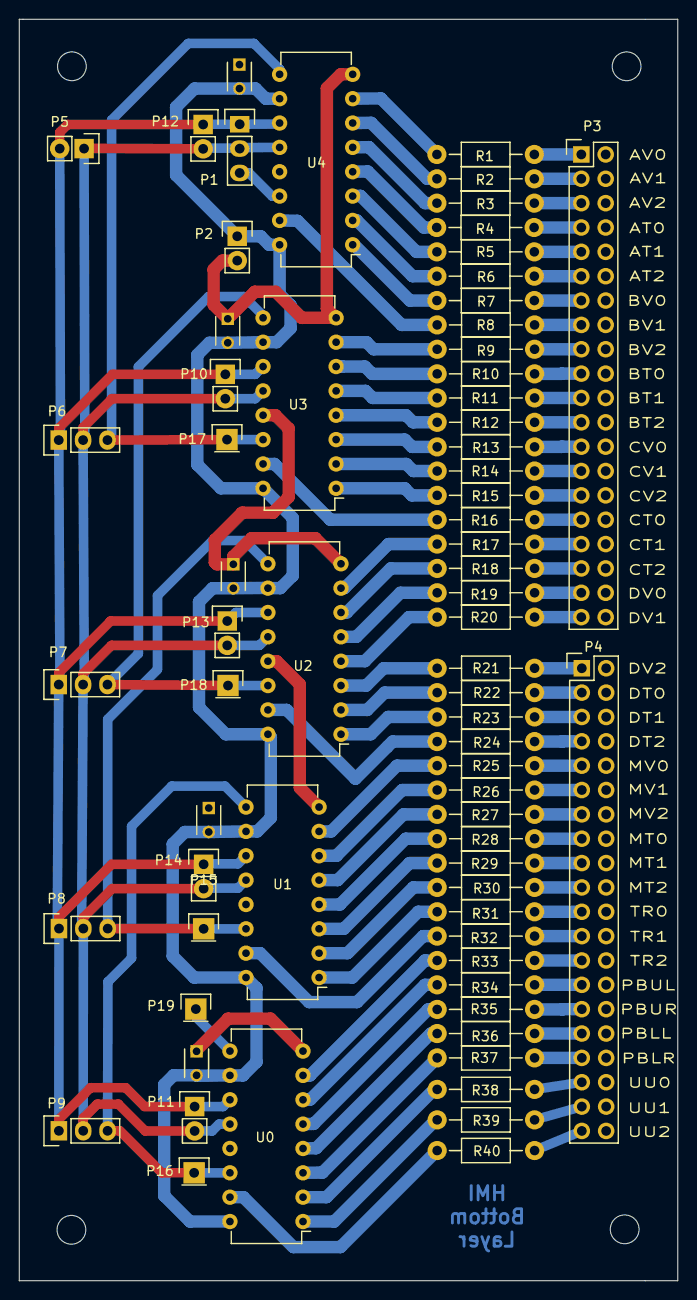
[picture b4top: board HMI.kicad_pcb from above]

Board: 2 copper layers, 68.7 x 131.6 mm, 73 parts (0 on the bottom side), 90 nets.

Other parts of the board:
H0, H1, H2, H3: MountingHole_3mm

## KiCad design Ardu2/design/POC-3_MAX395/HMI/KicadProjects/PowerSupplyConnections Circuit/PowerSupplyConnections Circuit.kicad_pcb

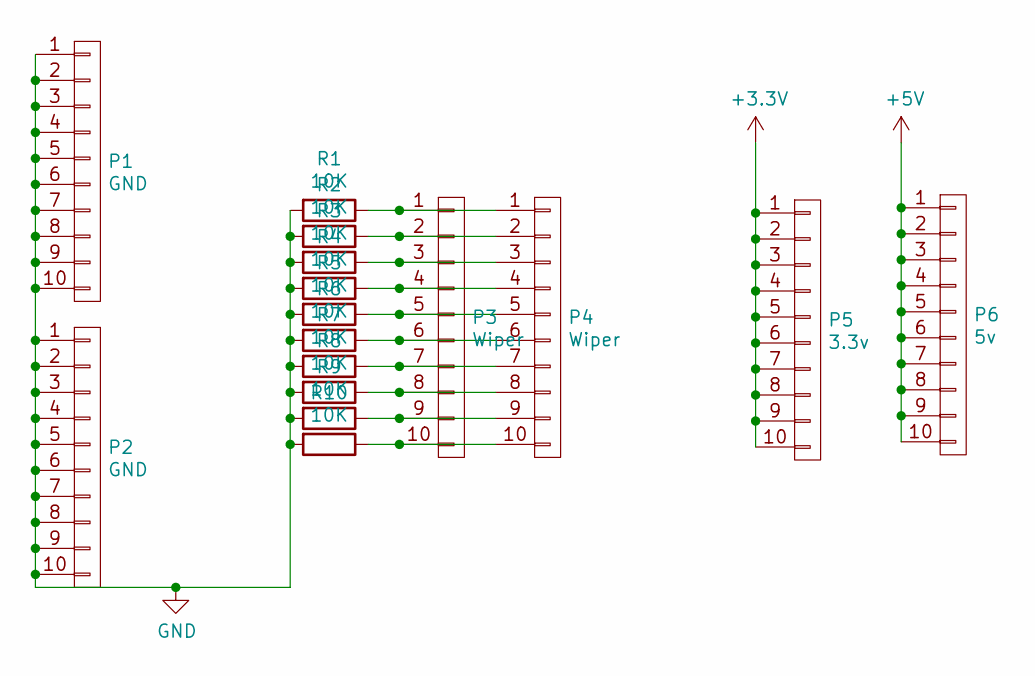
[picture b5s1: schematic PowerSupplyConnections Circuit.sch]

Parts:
P1, P2: GND; Pin_Header_Straight_1x10
P3, P4: Wiper; Pin_Header_Straight_1x10
P5: 3.3v; Pin_Header_Straight_1x10
P6: 5v; Pin_Header_Straight_1x10
R1, R2, R3, R4, R5, R6, R7, R8, R9, R10: 10K; Resistor_Horizontal_RM10mm

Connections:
+3V3: P5.1, P5.2, P5.3, P5.4, P5.5, P5.6, P5.7, P5.8, P5.9, P5.10
+5V: P6.1, P6.2, P6.3, P6.4, P6.5, P6.6, P6.7, P6.8, P6.9, P6.10
GND: P1.1, P1.2, P1.3, P1.4, P1.5, P1.6, P1.7, P1.8, P1.9, P1.10, P2.1, P2.2, P2.3, P2.4, P2.5, P2.6, P2.7, P2.8, P2.9, P2.10, R1.2, R2.2, R3.2, R4.2, R5.2, R6.2, R7.2, R8.2, R9.2, R10.2
unnamed: P3.1, P4.1, R1.1
unnamed: P3.2, P4.2, R2.1
unnamed: P3.3, P4.3, R3.1
unnamed: P3.4, P4.4, R4.1
unnamed: P3.5, P4.5, R5.1
unnamed: P3.6, P4.6, R6.1
unnamed: P3.7, P4.7, R7.1
unnamed: P3.8, P4.8, R8.1
unnamed: P3.9, P4.9, R9.1
unnamed: P3.10, P4.10, R10.1

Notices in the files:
parts and their libraries:
Copyright 2016 Accelerated Designs. All rights reserved.
